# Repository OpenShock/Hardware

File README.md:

# OpenShock-Hardware
KiCAD files for PCBs for transmitters and other hardware for [OpenShock](https://github.com/OpenShock/Firmware)

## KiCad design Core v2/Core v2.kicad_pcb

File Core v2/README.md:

## OpenShock Core V2.2L

#### Now only two layers!

#### Specs:
- ESP32-S3-WROOM-1
- USB-C
- In-built E-Stop button and AUX E-Stop port (3.5mm TRS jack)
- No USB-UART, uses built-in USB on ESP32-S3
- 3.3v regulator
- More compact than v1
- Footprint 40mm x 56mm

#### Important ordering information:
- PCB Thickness: **1.0mm**
- **2** Layers
- Impedence Controlled for JLCPCB's 1.0mm stackup
- Edge Rails in source files are not attached, and are not included in JLC gerbers
- **Standard PCBA** only (As of writing, Economy PCBA is unsupported for the ESP32-S3 modules due to solder reflow curve requirements)

JLCPCB may contact you about a couple of things:

- WS2812B-Minis may incur an extra component baking fee (~$8-10)
- Rotations of WS2812B-Mini and Antenna. Ensure that they match these examples:

#### Redlines (v2.0) (Solved in v2.1+):
- R1 (high side pullup for RF TX level-shifting) was causing unwanted RF signals when IO1 was Hi-Z/Input Enabled.
- EN pin missing debounce capacitor.

#### Redlines (v2.1):
- To be discovered.

#### Redlines (v2.2):
- To be discovered.

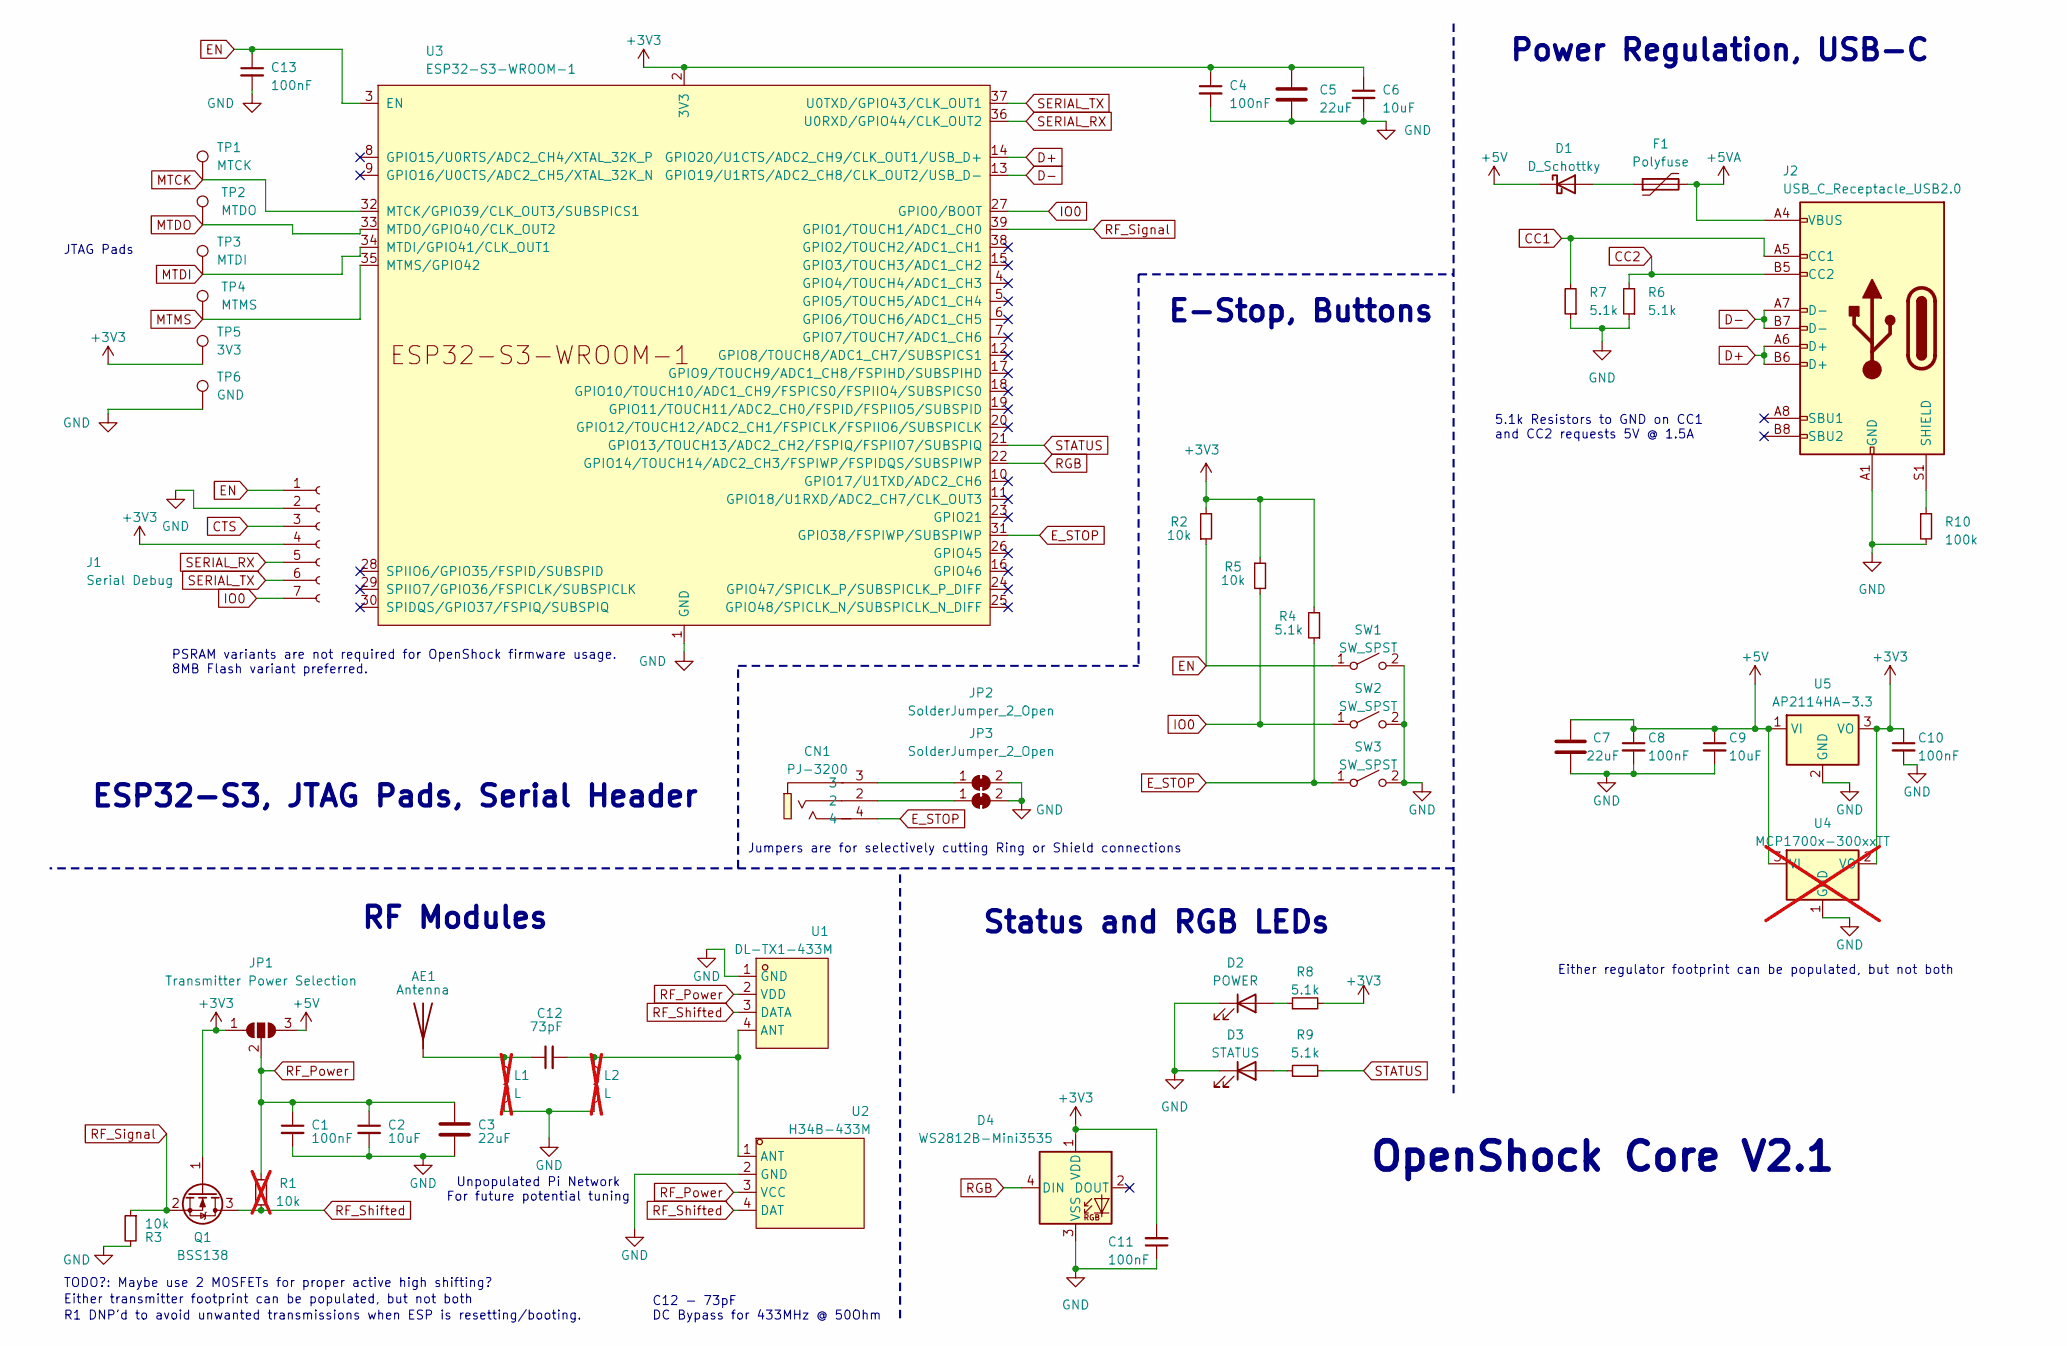
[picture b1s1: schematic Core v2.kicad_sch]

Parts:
AE1: Antenna; Pin_D1.0mm_L10.0mm
C1, C4, C8, C10, C11, C13: 100nF; C_0603_1608Metric_Pad1.08x0.95mm_HandSolder
C2, C6, C9: 10uF; C_0603_1608Metric_Pad1.08x0.95mm_HandSolder
C3, C5, C7: 22uF; C_0805_2012Metric_Pad1.18x1.45mm_HandSolder
C12: 73pF; C_0603_1608Metric_Pad1.08x0.95mm_HandSolder
CN1: PJ-3200; AUDIO-TH_PJ-3200; LCSC Part C2689690
D1: D_Schottky; D_SOD-123
D2: POWER; LED_0603_1608Metric_Pad1.05x0.95mm_HandSolder
D3: STATUS; LED_0603_1608Metric_Pad1.05x0.95mm_HandSolder
D4: WS2812B-Mini3535; LED_WS2812B-Mini_3.5x3.5mm_P1.75mm
F1: Polyfuse; Fuse_1206_3216Metric_Pad1.42x1.75mm_HandSolder
J1: Serial Debug; 1X07_LOCK
J2: USB_C_Receptacle_USB2.0; HRO-TYPE-C-31-M-12-HandSoldering_ABPads
JP1: Transmitter Power Selection; SolderJumper-3_P1.3mm_Open_RoundedPad1.0x1.5mm
JP2, JP3: SolderJumper_2_Open; SolderJumper-2_P1.3mm_Bridged_RoundedPad1.0x1.5mm
L1, L2: L; L_0603_1608Metric_Pad1.05x0.95mm_HandSolder; not fitted
Q1: BSS138; SOT-23
R1: 10k; R_0603_1608Metric_Pad0.98x0.95mm_HandSolder; not fitted
R2, R3, R5: 10k; R_0603_1608Metric_Pad0.98x0.95mm_HandSolder
R4, R6, R7, R8, R9: 5.1k; R_0603_1608Metric_Pad0.98x0.95mm_HandSolder
R10: 100k; R_0603_1608Metric_Pad0.98x0.95mm_HandSolder
SW1, SW2, SW3: SW_SPST; SW_PUSH_6mm_customized
TP1: MTCK; TestPoint_Pad_1.0x1.0mm
TP2: MTDO; TestPoint_Pad_1.0x1.0mm
TP3: MTDI; TestPoint_Pad_1.0x1.0mm
TP4: MTMS; TestPoint_Pad_1.0x1.0mm
TP5: 3V3; TestPoint_Pad_1.0x1.0mm
TP6: GND; TestPoint_Pad_1.0x1.0mm
U1: DL-TX1-433M; WIELM-TH_DL-TX1-433M; LCSC Part C381160
U2: H34B-433M; WIRELM-TH_H34S-433M; LCSC Part C89460
U3: ESP32-S3-WROOM-1
U4: MCP1700x-300xxTT; SOT-23_Handsoldering; not fitted
U5: AP2114HA-3.3; SOT-223-3_TabPin2

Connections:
+3V3: C4.1, C5.1, C6.1, C10.1, C11.2, D4.1 (VDD), J1.4, JP1.1 (A), Q1.1 (G), R2.2, R4.2, R5.1, R8.2, TP5.1, U3.2 (3V3), U4.2 (VO), U5.3 (VO)
+5V: C7.1, C8.1, C9.1, D1.1 (K), JP1.3 (B), U4.3 (VI), U5.1 (VI)
+5VA: F1.2, J2.A4 (VBUS), J2.A9 (VBUS), J2.B4 (VBUS), J2.B9 (VBUS)
CC1: J2.A5 (CC1), R7.2
CC2: J2.B5 (CC2), R6.2
CTS: J1.3
D+: J2.A6 (D+), J2.B6 (D+), U3.14 (GPIO20/U1CTS/ADC2_CH9/CLK_OUT1/USB_D+)
D-: J2.A7 (D-), J2.B7 (D-), U3.13 (GPIO19/U1RTS/ADC2_CH8/CLK_OUT2/USB_D-)
EN: C13.1, J1.1, R2.1, SW1.1 (A), U3.3 (EN)
E_STOP: CN1.4, R4.1, SW3.1 (A), U3.31 (GPIO38/FSPIWP/SUBSPIWP)
GND: C1.2, C2.2, C3.2, C4.2, C5.2, C6.2, C7.2, C8.2, C9.2, C10.2, C11.1, C13.2, D2.1 (K), D3.1 (K), D4.3 (VSS), J1.2, J2.A1 (GND), J2.A12 (GND), J2.B1 (GND), J2.B12 (GND), JP2.2 (B), JP3.2 (B), L1.2, L2.2, R3.2, R6.1, R7.1, R10.2, SW1.2 (B), SW2.2 (B), SW3.2 (B), TP6.1, U1.1 (GND), U2.2 (GND), U3.1 (GND), U3.40 (GND), U3.41 (GND), U4.1 (GND), U5.2 (GND)
IO0: J1.7, R5.2, SW2.1 (A), U3.27 (GPIO0/BOOT)
MTCK: TP1.1, U3.32 (MTCK/GPIO39/CLK_OUT3/SUBSPICS1)
MTDI: TP3.1, U3.34 (MTDI/GPIO41/CLK_OUT1)
MTDO: TP2.1, U3.33 (MTDO/GPIO40/CLK_OUT2)
MTMS: TP4.1, U3.35 (MTMS/GPIO42)
unnamed: AE1.1 (A), C12.1, L1.1
unnamed: D1.2 (A), F1.1
unnamed: D2.2 (A), R8.1
unnamed: D3.2 (A), R9.1
unnamed: J2.S1 (SHIELD), R10.1
unnamed: CN1.3, JP2.1 (A)
unnamed: CN1.2, JP3.1 (A)
unnamed: C12.2, L2.1, U1.4 (ANT), U2.1 (ANT)
RF_Power: C1.1, C2.1, C3.1, JP1.2 (C), R1.1, U1.2 (VDD), U2.3 (VCC)
RF_Shifted: Q1.3 (D), R1.2, U1.3 (DATA), U2.4 (DAT)
RF_Signal: Q1.2 (S), R3.1, U3.39 (GPIO1/TOUCH1/ADC1_CH0)
RGB: D4.4 (DIN), U3.22 (GPIO14/TOUCH14/ADC2_CH3/FSPIWP/FSPIDQS/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)
SERIAL_RX: J1.5, U3.36 (U0RXD/GPIO44/CLK_OUT2)
SERIAL_TX: J1.6, U3.37 (U0TXD/GPIO43/CLK_OUT1)
STATUS: R9.2, U3.21 (GPIO13/TOUCH13/ADC2_CH2/FSPIQ/FSPIIO7/S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)

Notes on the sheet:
RF Modules
JTAG Pads
PSRAM variants are not required for OpenShock firmware usage. 8MB Flash variant preferred.
OpenShock Core V2.1
E-Stop, Buttons
Power Regulation, USB-C
5.1k Resistors to GND on CC1 and CC2 requests 5V @ 1.5A
Unpopulated Pi Network For future potential tuning
R1 DNP'd to avoid unwanted transmissions when ESP is resetting/booting.
C12 - 73pF DC Bypass for 433MHz @ 50Ohm
Jumpers are for selectively cutting Ring or Shield connections
Status and RGB LEDs
Either transmitter footprint can be populated, but not both
Either regulator footprint can be populated, but not both
TODO?: Maybe use 2 MOSFETs for proper active high shifting?
ESP32-S3, JTAG Pads, Serial Header

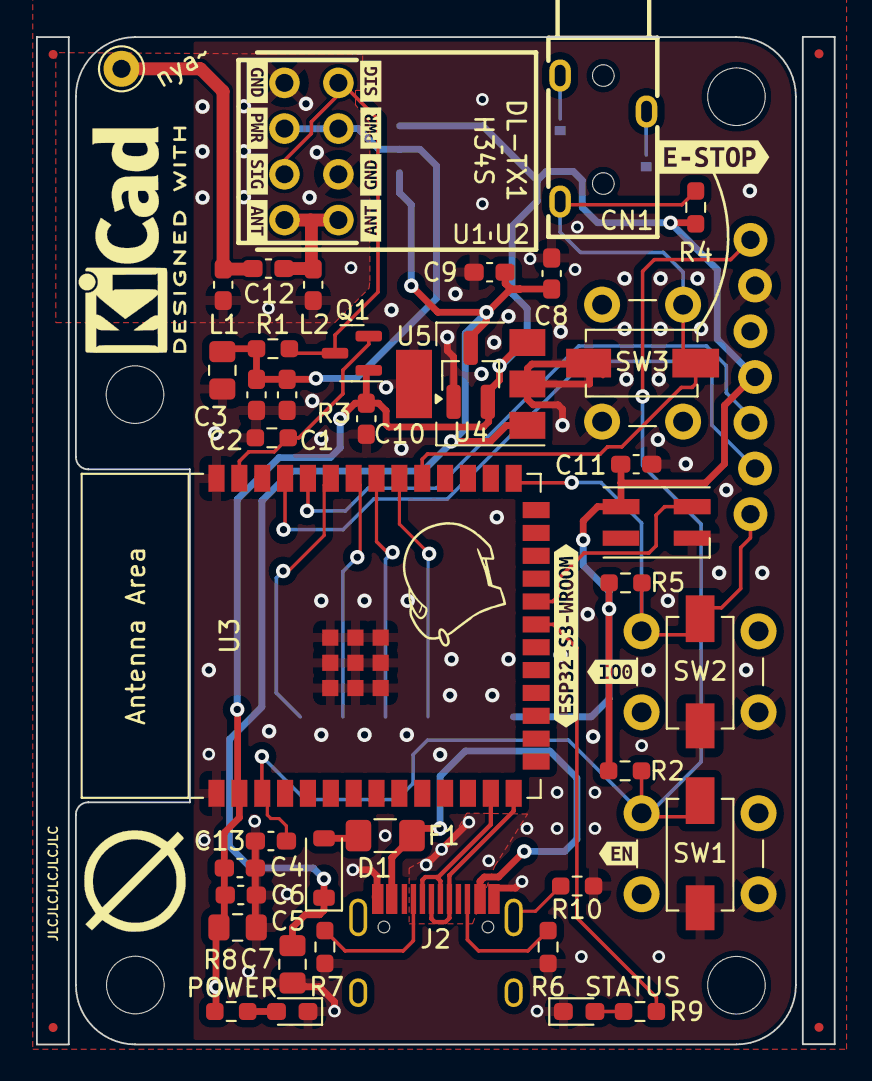
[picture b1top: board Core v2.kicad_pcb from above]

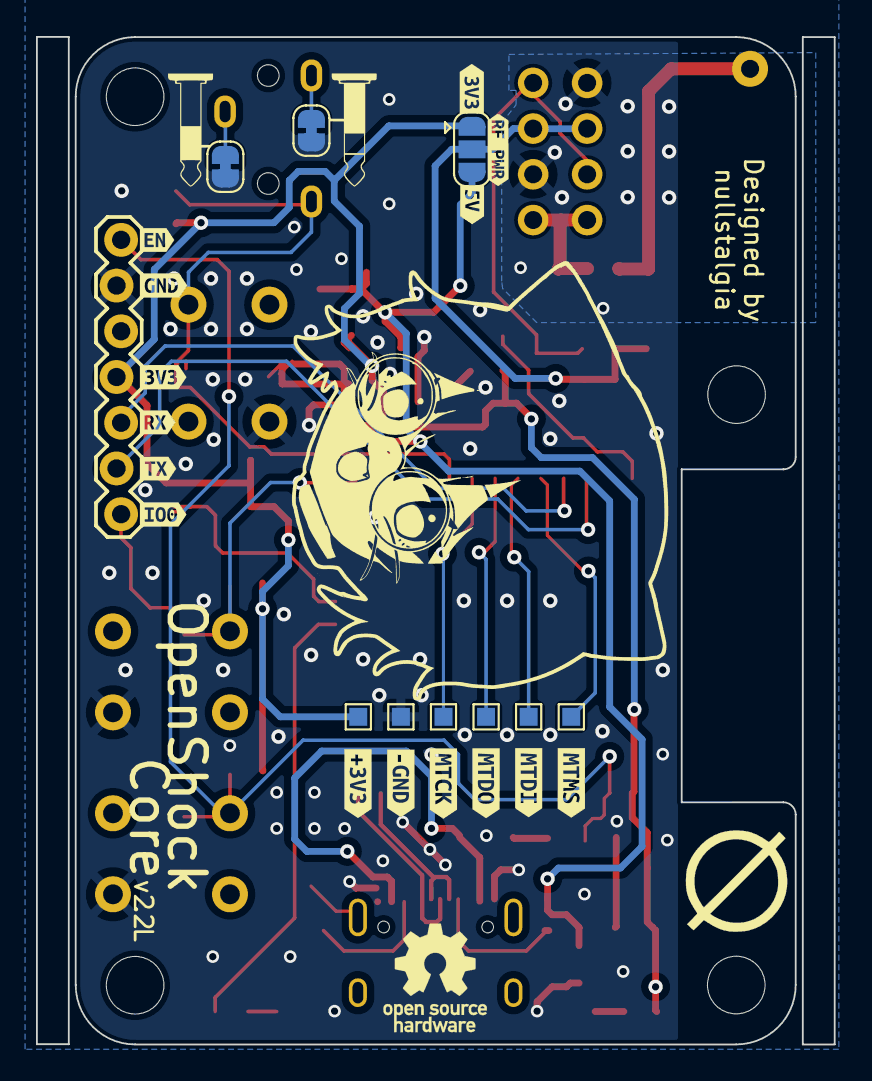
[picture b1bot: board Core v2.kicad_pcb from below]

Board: 2 copper layers, 44.3 x 56.0 mm, 83 parts (25 on the bottom side), 30 nets.

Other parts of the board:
FID1, FID1#2, FID4, FID4#2: Fiducial; Fiducial_0.5mm_Mask1mm
kibuzzard-63FC1B9A: G***; kibuzzard-63FC1B9A
kibuzzard-63FC1BA4: G***; kibuzzard-63FC1BA4
kibuzzard-63FC1BB3: G***; kibuzzard-63FC1BB3
kibuzzard-65FD518D: G***; kibuzzard-65FD518D
kibuzzard-65FD5191: G***; kibuzzard-65FD5191
kibuzzard-658A25BD: G***; kibuzzard-658A25BD
kibuzzard-658A26D4: G***; kibuzzard-658A26D4
kibuzzard-658A26D7: G***; kibuzzard-658A26D7
kibuzzard-658A26DB: G***; kibuzzard-658A26DB
kibuzzard-658A27EA: G***; kibuzzard-658A27EA
kibuzzard-658A42A3, kibuzzard-658A42A3#2: G***; kibuzzard-658A42A3
kibuzzard-658A42A8, kibuzzard-658A42A8#2: G***; kibuzzard-658A42A8
kibuzzard-658A42AC, kibuzzard-658A42AC#2: G***; kibuzzard-658A42AC
kibuzzard-658A264C: G***; kibuzzard-658A264C
kibuzzard-658A265D: G***; kibuzzard-658A265D
kibuzzard-658A269D: G***; kibuzzard-658A269D
kibuzzard-658A429F, kibuzzard-658A429F#2: G***; kibuzzard-658A429F
kibuzzard-658A779F: G***; kibuzzard-658A779F
kibuzzard-658A2647: G***; kibuzzard-658A2647
kibuzzard-658A2652: G***; kibuzzard-658A2652
kibuzzard-658A2659: G***; kibuzzard-658A2659
kibuzzard-658A2661: G***; kibuzzard-658A2661
kibuzzard-658A4835: G***; kibuzzard-658A4835

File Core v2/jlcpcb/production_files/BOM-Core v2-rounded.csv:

Comment,Designator,Footprint,LCSC
100nF,"C1,C10,C11,C13,C4,C8",C_0603_1608Metric_Pad1.08x0.95mm_HandSolder,C14663
10uF,"C2,C6,C9",C_0603_1608Metric_Pad1.08x0.95mm_HandSolder,C19702
POWER,D2,LED_0603_1608Metric_Pad1.05x0.95mm_HandSolder,C2286
5.1k,"R4,R6,R7,R8,R9",R_0603_1608Metric_Pad0.98x0.95mm_HandSolder,C23186
100k,R10,R_0603_1608Metric_Pad0.98x0.95mm_HandSolder,C25803
10k,"R2,R3,R5",R_0603_1608Metric_Pad0.98x0.95mm_HandSolder,C25804
PJ-3200,CN1,AUDIO-TH_PJ-3200,C2689690
USB_C_Receptacle_USB2.0,J2,HRO-TYPE-C-31-M-12-HandSoldering_ABPads,C2760486
ESP32-S3-WROOM-1,U3,ESP32-S3-WROOM-1,C2913198
SW_SPST,"SW1,SW2,SW3",SW_PUSH_6mm_customized,C445493
22uF,"C3,C5,C7",C_0805_2012Metric_Pad1.18x1.45mm_HandSolder,C45783
73pF,C12,C_0603_1608Metric_Pad1.08x0.95mm_HandSolder,C458970
AP2114HA-3.3,U5,SOT-223-3_TabPin2,C460314
WS2812B-Mini3535,D4,LED_WS2812B-Mini_3.5x3.5mm_P1.75mm,C527089
STATUS,D3,LED_0603_1608Metric_Pad1.05x0.95mm_HandSolder,C72038
BSS138,Q1,SOT-23,C8490
D_Schottky,D1,D_SOD-123,C8598
Polyfuse,F1,Fuse_1206_3216Metric_Pad1.42x1.75mm_HandSolder,C883133
Antenna,AE1,Pin_D1.0mm_L10.0mm,C89805

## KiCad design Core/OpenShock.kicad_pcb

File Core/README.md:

## OpenShock Core

v1.1

#### Specs:
- ESP32-S3-WROOM-1
- USB-C
- Pinouts for several transmitters for DIY users
- In-built E-Stop button and AUX E-Stop port (3.5mm TRS jack)
- No USB-UART, uses built-in USB on ESP32-S3
- 3.3v regulator
- Footprint 45.2mm x 75.7mm

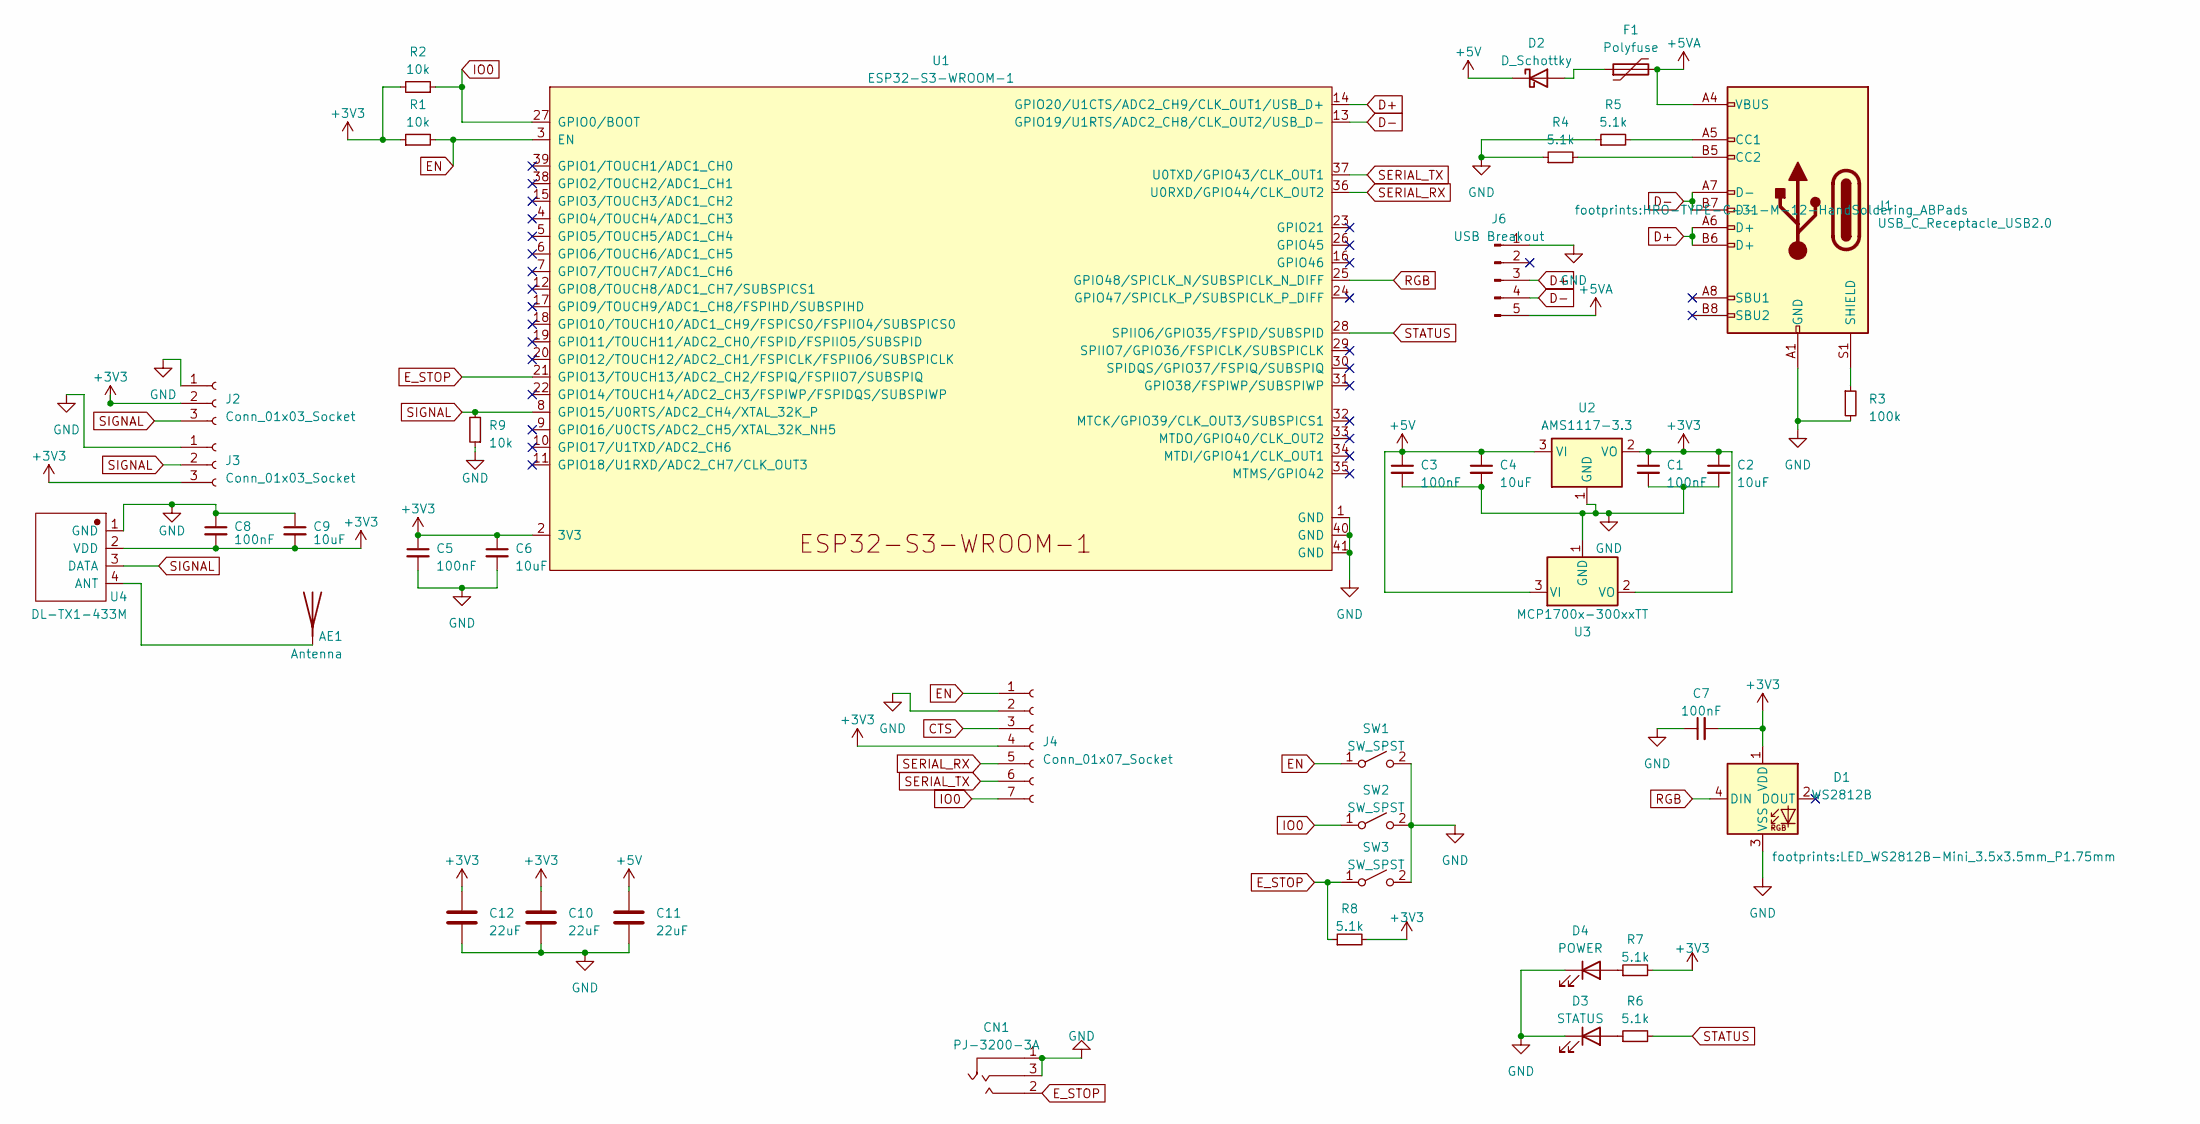
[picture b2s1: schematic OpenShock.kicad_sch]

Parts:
AE1: Antenna; PinHeader_1x01_P2.54mm_Vertical
C1, C3, C5, C7, C8: 100nF; C_0603_1608Metric_Pad1.08x0.95mm_HandSolder
C2, C4, C6, C9: 10uF; C_0603_1608Metric_Pad1.08x0.95mm_HandSolder
C10, C11, C12: 22uF; C_0805_2012Metric_Pad1.18x1.45mm_HandSolder
CN1: PJ-3200-3A; AUDIO-TH_PJ-3200-3A
D1: WS2812B; LED_WS2812B-Mini_3.5x3.5mm_P1.75mm
D2: D_Schottky; D_SOD-123
D3: STATUS; LED_0603_1608Metric_Pad1.05x0.95mm_HandSolder
D4: POWER; LED_0603_1608Metric_Pad1.05x0.95mm_HandSolder
F1: Polyfuse; Fuse_1206_3216Metric_Pad1.42x1.75mm_HandSolder
J1: USB_C_Receptacle_USB2.0; HRO-TYPE-C-31-M-12-HandSoldering_ABPads
J2, J3: Conn_01x03_Socket; PinSocket_1x03_P2.54mm_Vertical
J4: Conn_01x07_Socket; 1X07_LOCK
J6: USB Breakout; PinSocket_1x05_P2.54mm_Vertical
R1, R2, R9: 10k; R_0603_1608Metric_Pad0.98x0.95mm_HandSolder
R3: 100k; R_0603_1608Metric_Pad0.98x0.95mm_HandSolder
R4, R5, R6, R7, R8: 5.1k; R_0603_1608Metric_Pad0.98x0.95mm_HandSolder
SW1, SW2: SW_SPST; SW_PUSH_6mm_customized
SW3: SW_SPST; SW_PUSH-12mm
U1: ESP32-S3-WROOM-1
U2: AMS1117-3.3; SOT-223-3_TabPin2
U3: MCP1700x-300xxTT; SOT-23_Handsoldering
U4: DL-TX1-433M; WIELM-TH_DL-TX1-433M

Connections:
+3V3: C1.1, C2.1, C5.1, C6.1, C7.2, C8.2, C9.2, C10.1, C12.1, D1.1 (VDD), J2.2, J3.3, J4.4, R1.1, R2.2, R7.2, R8.2, U1.2 (3V3), U2.2 (VO), U3.2 (VO), U4.2 (VDD)
+5V: C3.1, C4.1, C11.1, D2.1 (K), U2.3 (VI), U3.3 (VI)
+5VA: F1.2, J1.A4 (VBUS), J1.A9 (VBUS), J1.B4 (VBUS), J1.B9 (VBUS), J6.5
CTS: J4.3
D+: J1.A6 (D+), J1.B6 (D+), J6.3, U1.14 (GPIO20/U1CTS/ADC2_CH9/CLK_OUT1/USB_D+)
D-: J1.A7 (D-), J1.B7 (D-), J6.4, U1.13 (GPIO19/U1RTS/ADC2_CH8/CLK_OUT2/USB_D-)
EN: J4.1, R1.2, SW1.1 (A), U1.3 (EN)
E_STOP: CN1.2, R8.1, SW3.1 (A), U1.21 (GPIO13/TOUCH13/ADC2_CH2/FSPIQ/FSPIIO7/S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)
GND: C1.2, C2.2, C3.2, C4.2, C5.2, C6.2, C7.1, C8.1, C9.1, C10.2, C11.2, C12.2, CN1.1, CN1.3, D1.3 (VSS), D3.1 (K), D4.1 (K), J1.A1 (GND), J1.A12 (GND), J1.B1 (GND), J1.B12 (GND), J2.1, J3.1, J4.2, J6.1, R3.2, R4.1, R5.1, R9.1, SW1.2 (B), SW2.2 (B), SW3.2 (B), U1.1 (GND), U1.40 (GND), U1.41 (GND), U2.1 (GND), U3.1 (GND), U4.1 (GND)
IO0: J4.7, R2.1, SW2.1 (A), U1.27 (GPIO0/BOOT)
unnamed: AE1.1 (A), U4.4 (ANT)
unnamed: D2.2 (A), F1.1
unnamed: D3.2 (A), R6.1
unnamed: D4.2 (A), R7.1
unnamed: J1.A5 (CC1), R5.2
unnamed: J1.B5 (CC2), R4.2
unnamed: J1.S1 (SHIELD), R3.1
RGB: D1.4 (DIN), U1.25 (GPIO48/SPICLK_N/SUBSPICLK_N_DIFF)
SERIAL_RX: J4.5, U1.36 (U0RXD/GPIO44/CLK_OUT2)
SERIAL_TX: J4.6, U1.37 (U0TXD/GPIO43/CLK_OUT1)
SIGNAL: J2.3, J3.2, R9.2, U1.8 (GPIO15/U0RTS/ADC2_CH4/XTAL_32K_P), U4.3 (DATA)
STATUS: R6.2, U1.28 (SPIIO6/GPIO35/FSPID/SUBSPID)

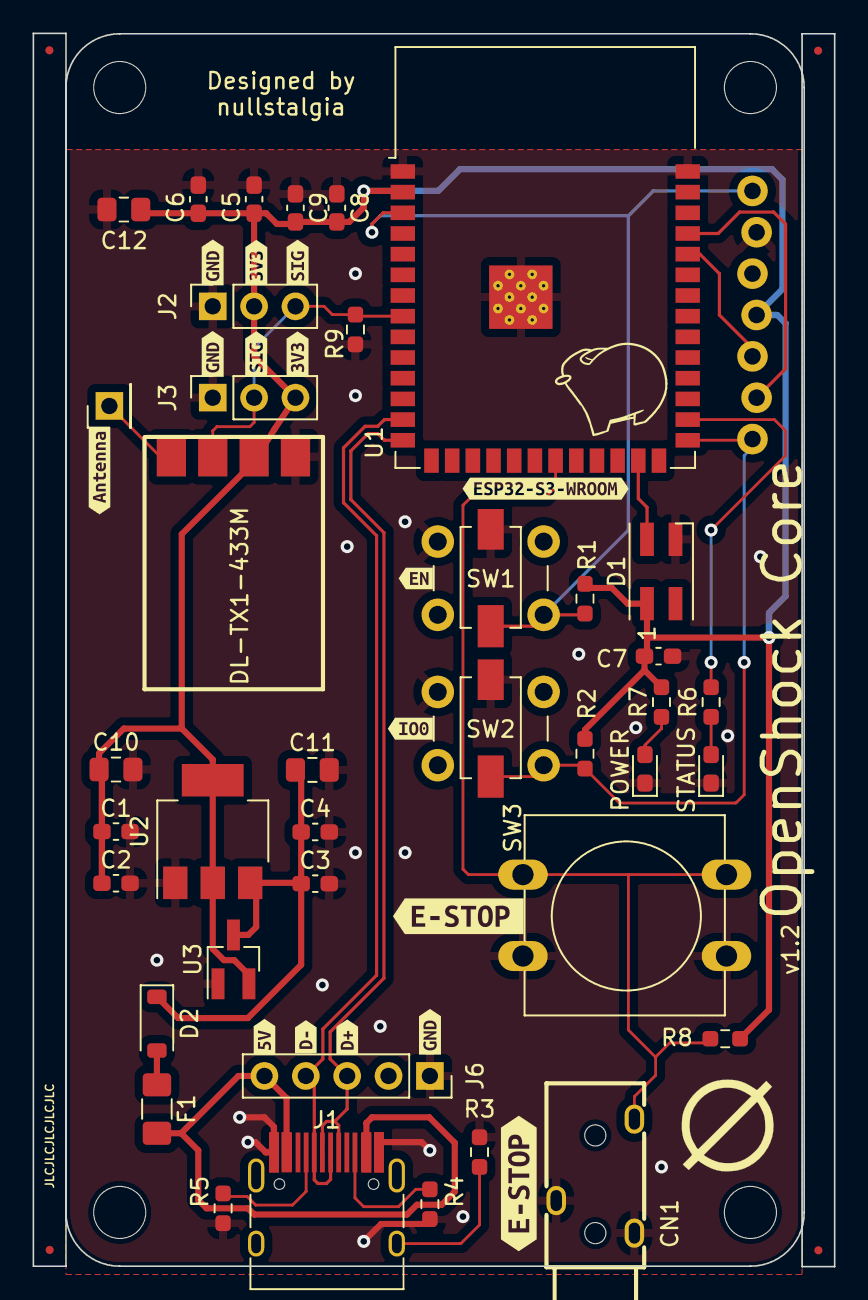
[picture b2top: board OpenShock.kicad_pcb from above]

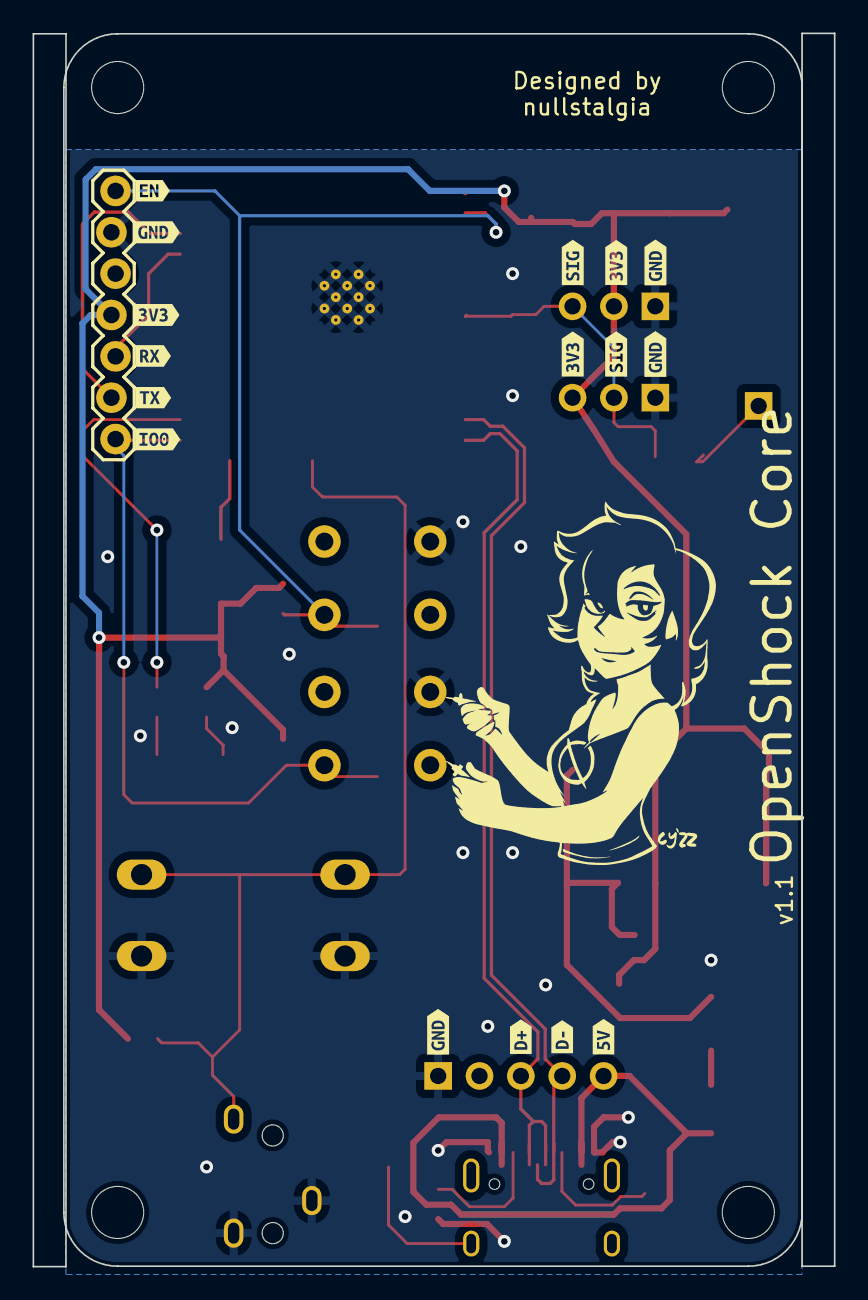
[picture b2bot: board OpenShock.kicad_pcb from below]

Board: 2 copper layers, 49.2 x 75.7 mm, 75 parts (17 on the bottom side), 21 nets.

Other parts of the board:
FID1, FID4, FID4#2: Fiducial; Fiducial_0.5mm_Mask1mm
kibuzzard-63FC1A6B, kibuzzard-63FC1A6B#2: G***; kibuzzard-63FC1A6B
kibuzzard-63FC1B9A: G***; kibuzzard-63FC1B9A
kibuzzard-63FC1BA4: G***; kibuzzard-63FC1BA4
kibuzzard-63FC1BB3: G***; kibuzzard-63FC1BB3
kibuzzard-63FC1BEB: G***; kibuzzard-63FC1BEB
kibuzzard-63FC2C9B: G***; kibuzzard-63FC2C9B
kibuzzard-63FC2CA9: G***; kibuzzard-63FC2CA9
kibuzzard-63FC2CB3: G***; kibuzzard-63FC2CB3
kibuzzard-63FC2CBA: G***; kibuzzard-63FC2CBA
kibuzzard-63FC2CC3: G***; kibuzzard-63FC2CC3
kibuzzard-63FC2CD0: G***; kibuzzard-63FC2CD0
kibuzzard-63FC15BA: G***; kibuzzard-63FC15BA
kibuzzard-63FC17E4, kibuzzard-63FC17E4#2: G***; kibuzzard-63FC17E4
kibuzzard-63FC17F2, kibuzzard-63FC17F2#2: G***; kibuzzard-63FC17F2
kibuzzard-63FC17FB, kibuzzard-63FC17FB#2: G***; kibuzzard-63FC17FB
kibuzzard-63FC19D3, kibuzzard-63FC19D3#2: G***; kibuzzard-63FC19D3
kibuzzard-63FC180E, kibuzzard-63FC180E#2: G***; kibuzzard-63FC180E
kibuzzard-63FC195C, kibuzzard-63FC195C#2, kibuzzard-63FC195C#3, kibuzzard-63FC195C#4: G***; kibuzzard-63FC195C
kibuzzard-63FC1570: G***; kibuzzard-63FC1570
kibuzzard-63FC1972, kibuzzard-63FC1972#2: G***; kibuzzard-63FC1972
kibuzzard-63FC1979, kibuzzard-63FC1979#2: G***; kibuzzard-63FC1979

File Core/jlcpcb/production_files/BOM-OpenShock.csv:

Comment,Designator,Footprint,LCSC
SW_SPST,"SW1,SW2",SW_PUSH_6mm_customized,C13828
100nF,"C1,C3,C5,C7,C8",C_0603_1608Metric_Pad1.08x0.95mm_HandSolder,C14663
USB_C_Receptacle_USB2.0,J1,HRO-TYPE-C-31-M-12-HandSoldering_ABPads,C165948
Polyfuse,F1,Fuse_1206_3216Metric_Pad1.42x1.75mm_HandSolder,C17888
10uF,"C2,C4,C6,C9",C_0603_1608Metric_Pad1.08x0.95mm_HandSolder,C19702
POWER,D4,LED_0603_1608Metric_Pad1.05x0.95mm_HandSolder,C2286
5.1k,"R4,R5,R6,R7,R8",R_0603_1608Metric_Pad0.98x0.95mm_HandSolder,C23186
100k,R3,R_0603_1608Metric_Pad0.98x0.95mm_HandSolder,C25803
10k,"R1,R2,R9",R_0603_1608Metric_Pad0.98x0.95mm_HandSolder,C25804
ESP32-S3-WROOM-1,U1,ESP32-S3-WROOM-1,C2913204
DL-TX1-433M,U4,WIELM-TH_DL-TX1-433M,C381160
22uF,"C10,C11,C12",C_0805_2012Metric_Pad1.18x1.45mm_HandSolder,C45783
WS2812B,D1,LED_WS2812B-Mini_3.5x3.5mm_P1.75mm,C527089
AMS1117-3.3,U2,SOT-223-3_TabPin2,C6186
PJ-3200-3A,CN1,AUDIO-TH_PJ-3200-3A,C709202
STATUS,D3,LED_0603_1608Metric_Pad1.05x0.95mm_HandSolder,C72043
D_Schottky,D2,D_SOD-123,C8598
Antenna,AE1,PinHeader_1x01_P2.54mm_Vertical,C961609
Fiducial,FID4,Fiducial_0.5mm_Mask1mm,

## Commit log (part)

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2023-04-06 Add CERN OHL-S
2023-04-06 Core v1.1
2023-07-17 Add schematic PDF and pics
2023-08-24 .gitignore was hiding exported BOM + PNP for JLC ordering
2023-12-02 OpenShock Core V1.2, fixes dumb short between 3v3 and GND
2024-01-28 Core V2!
2024-02-09 Add ordering info for Core V2
2024-03-31 Remove R1 from Core V2.0 BOM/CPL
2024-05-17 Core V2.1 KiCad + JLC Files
2024-05-17 Core V2.2 KiCad + JLC Files
2024-05-17 Core V1 and V2 case files (3MF, STL, STEP)
2024-05-17 Fix 2.2L images
2024-05-17 Update README image, link to Firmware repo
